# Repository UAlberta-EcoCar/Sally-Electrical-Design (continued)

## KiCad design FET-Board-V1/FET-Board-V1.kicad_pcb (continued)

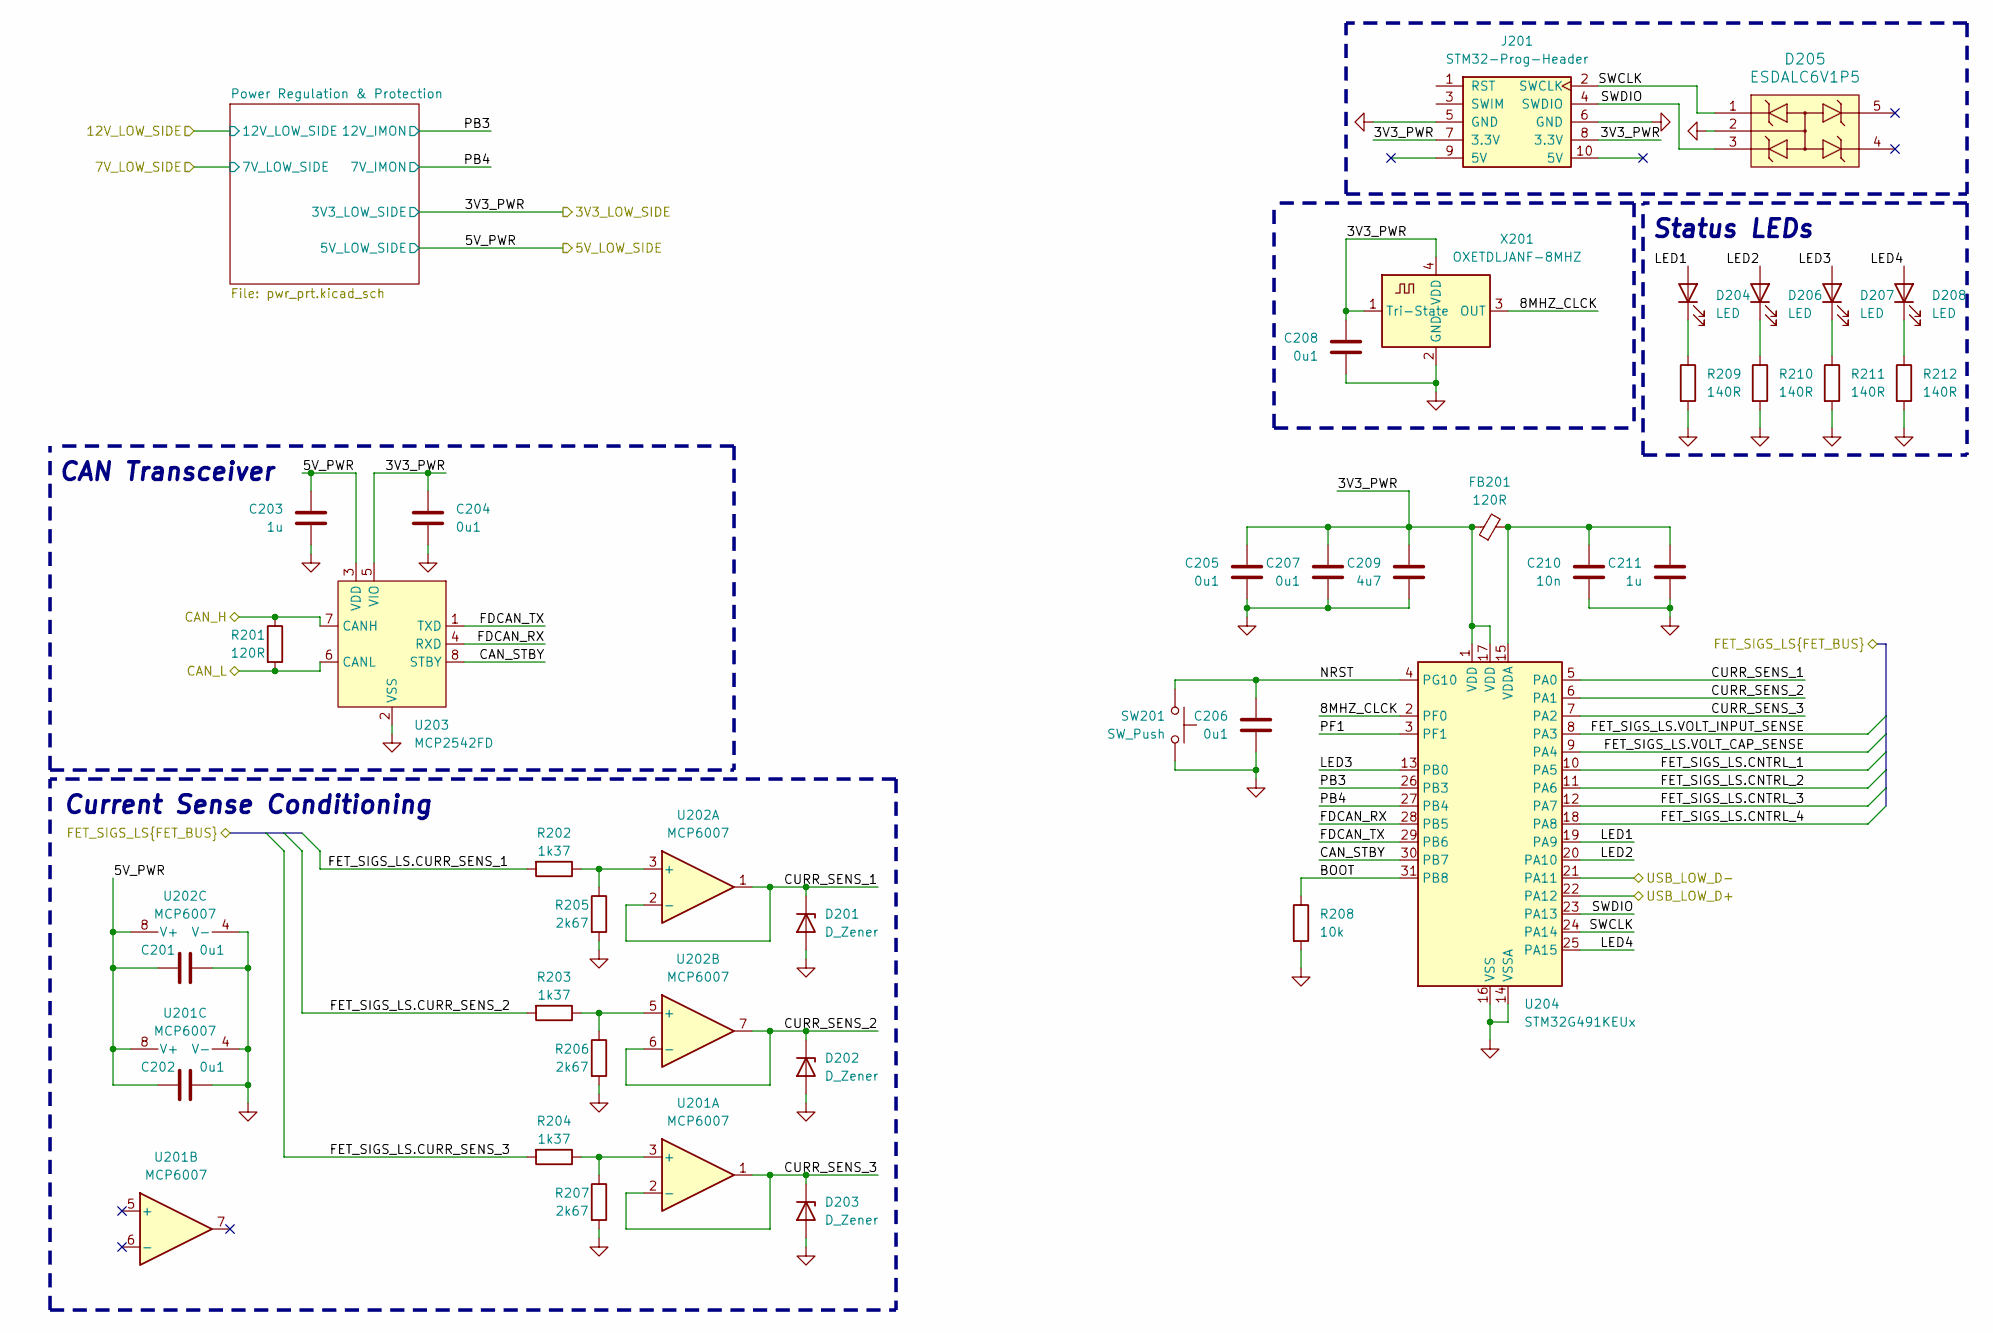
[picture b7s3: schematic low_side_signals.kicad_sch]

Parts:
C201, C202, C204, C205, C206, C207, C208: 0u1; C_0603_1608Metric
C203, C211: 1u; C_0603_1608Metric
C209: 4u7; C_0603_1608Metric
C210: 10n; C_0603_1608Metric
D201, D202, D203: D_Zener; D_0603_1608Metric
D204, D206, D207, D208: LED; LED_0603_1608Metric
D205: ESDALC6V1P5
FB201: 120R; L_0603_1608Metric
J201: STM32-Prog-Header; IDC-STM32-Prog-Header_2x05_P2.54mm_Vertical
R201: 120R; R_0603_1608Metric
R202, R203, R204: 1k37; R_0603_1608Metric
R205, R206, R207: 2k67; R_0603_1608Metric
R208: 10k; R_0603_1608Metric
R209, R210, R211, R212: 140R; R_0603_1608Metric
SW201: SW_Push; SW_PUSH_6mm
U201, U202: MCP6007; SOIC-8_3.9x4.9mm_P1.27mm
U203: MCP2542FD; SOIC-8_3.9x4.9mm_P1.27mm
U204: STM32G491KEUx; QFN-32-1EP_5x5mm_P0.5mm_EP3.45x3.45mm
X201: OXETDLJANF-8MHZ; Crystal_SMD_3225-4Pin_3.2x2.5mm

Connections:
5V_HS_NONISO: C201.1, C202.1, C203.1, U201.8 (V+), U202.8 (V+), U203.3 (VDD); also elsewhere on the board
/3V3_HIGH_SIDE: C204.1, C205.1, C207.1, C208.1, C209.1, FB201.1, J201.7 (3.3V), J201.8 (3.3V), U203.5 (VIO), U204.1 (VDD), U204.17 (VDD), X201.1 (Tri-State), X201.4 (VDD); also elsewhere on the board
/FET_SIGS_LS.CNTRL_1: U204.10 (PA5); also elsewhere on the board
/FET_SIGS_LS.CNTRL_2: U204.11 (PA6); also elsewhere on the board
/FET_SIGS_LS.CNTRL_3: U204.12 (PA7); also elsewhere on the board
/FET_SIGS_LS.CNTRL_4: U204.18 (PA8); also elsewhere on the board
/FET_SIGS_LS.CURR_SENS_1: R202.2; also elsewhere on the board
/FET_SIGS_LS.CURR_SENS_2: R203.2; also elsewhere on the board
/FET_SIGS_LS.CURR_SENS_3: R204.2; also elsewhere on the board
/FET_SIGS_LS.VOLT_CAP_SENSE: U204.9 (PA4); also elsewhere on the board
/FET_SIGS_LS.VOLT_INPUT_SENSE: U204.8 (PA3); also elsewhere on the board
/High Power Controls/CAN_H: R201.1, U203.7 (CANH); also elsewhere on the board
/High Power Controls/CAN_L: R201.2, U203.6 (CANL); also elsewhere on the board
/High Power Controls/USB_HIGH_D+: U204.22 (PA12); also elsewhere on the board
/High Power Controls/USB_HIGH_D-: U204.21 (PA11); also elsewhere on the board
/Low Power Controls/8MHZ_CLCK: U204.2 (PF0), X201.3 (OUT)
/Low Power Controls/BOOT: R208.1, U204.31 (PB8)
/Low Power Controls/CAN_STBY: U203.8 (STBY), U204.30 (PB7)
/Low Power Controls/CURR_SENS_1: D201.1 (K), U202.1, U202.2 (-), U204.5 (PA0)
/Low Power Controls/CURR_SENS_2: D202.1 (K), U202.6 (-), U202.7, U204.6 (PA1)
/Low Power Controls/CURR_SENS_3: D203.1 (K), U201.1, U201.2 (-), U204.7 (PA2)
/Low Power Controls/FDCAN_RX: U203.4 (RXD), U204.28 (PB5)
/Low Power Controls/FDCAN_TX: U203.1 (TXD), U204.29 (PB6)
/Low Power Controls/LED1: D204.2 (A), U204.19 (PA9)
/Low Power Controls/LED2: D206.2 (A), U204.20 (PA10)
/Low Power Controls/LED3: D207.2 (A), U204.13 (PB0)
/Low Power Controls/LED4: D208.2 (A), U204.25 (PA15)
/Low Power Controls/NRST: C206.1, SW201.2, U204.4 (PG10)
/Low Power Controls/PB3: U204.26 (PB3); also elsewhere on the board
/Low Power Controls/PB4: U204.27 (PB4); also elsewhere on the board
/Low Power Controls/PF1: U204.3 (PF1)
/Low Power Controls/SWCLK: D205.1, J201.2 (SWCLK), U204.24 (PA14)
/Low Power Controls/SWDIO: D205.3, J201.4 (SWDIO), U204.23 (PA13)
unnamed: D204.1 (K), R209.1
unnamed: D206.1 (K), R210.1
unnamed: D207.1 (K), R211.1
unnamed: D208.1 (K), R212.1
unnamed: R204.1, R207.1, U201.3 (+)
unnamed: R202.1, R205.1, U202.3 (+)
unnamed: R203.1, R206.1, U202.5 (+)
unnamed: C210.1, C211.1, FB201.2, U204.15 (VDDA)

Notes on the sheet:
Status LEDs
CAN Transceiver
Current Sense Conditioning

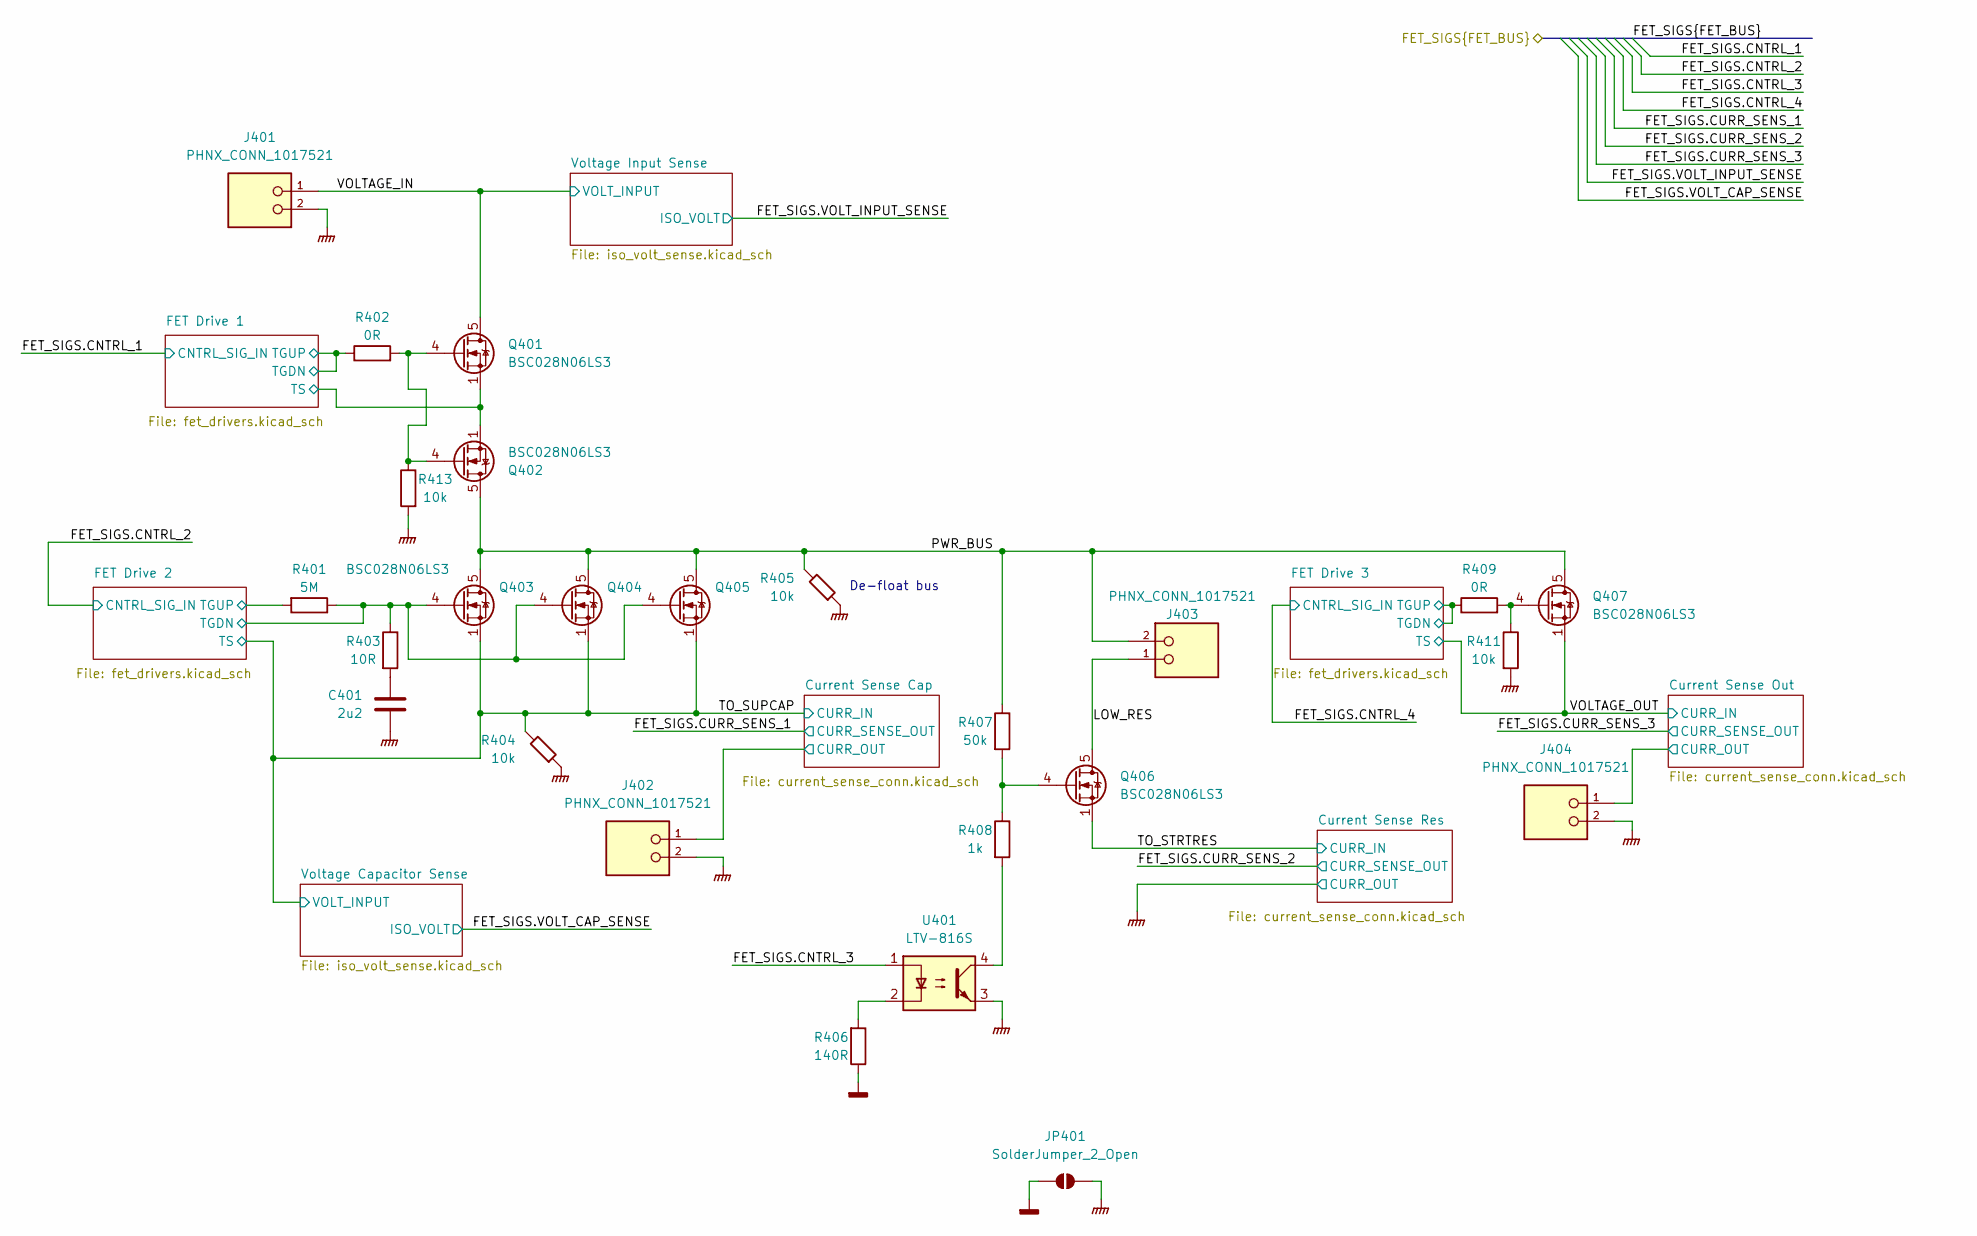
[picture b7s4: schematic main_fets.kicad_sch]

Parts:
C401: 2u2; C_0603_1608Metric
J401, J402, J403, J404: PHNX_CONN_1017521; PHOENIX_1017521; PARTREV 04.01.2018
JP401: SolderJumper_2_Open; SolderJumper-2_P1.3mm_Open_Pad1.0x1.5mm
Q401, Q402, Q403, Q404, Q405, Q406, Q407: BSC028N06LS3; TDSON-8-1
R401: 5M; R_0603_1608Metric
R402, R409: 0R; R_0603_1608Metric
R403: 10R; R_0603_1608Metric
R404, R405, R411, R413: 10k; R_0603_1608Metric
R406: 140R; R_0603_1608Metric
R407: 50k; R_0603_1608Metric
R408: 1k; R_0603_1608Metric
U401: LTV-816S; SMDIP-4_W9.53mm

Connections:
/FET_SIGS_LS.CNTRL_3: U401.1; also elsewhere on the board
/High Power Controls/Mains & FETS/Current Sense Cap/CURR_OUT: J402.1; also elsewhere on the board
/High Power Controls/Mains & FETS/Current Sense Out/CURR_OUT: J404.1; also elsewhere on the board
/High Power Controls/Mains & FETS/FET Drive 1/TGDN: R402.1; also elsewhere on the board
/High Power Controls/Mains & FETS/FET Drive 1/TS: Q401.1 (S), Q401.2 (S), Q401.3 (S), Q402.1 (S), Q402.2 (S), Q402.3 (S); also elsewhere on the board
/High Power Controls/Mains & FETS/FET Drive 2/TGDN: Q403.4 (G), Q404.4 (G), Q405.4 (G), R401.1, R403.1; also elsewhere on the board
/High Power Controls/Mains & FETS/FET Drive 2/TGUP: R401.2; also elsewhere on the board
/High Power Controls/Mains & FETS/FET Drive 3/TGDN: R409.1; also elsewhere on the board
/High Power Controls/Mains & FETS/LOW_RES: J403.1, Q406.5 (D)
/High Power Controls/Mains & FETS/PWR_BUS: J403.2, Q402.5 (D), Q403.5 (D), Q404.5 (D), Q405.5 (D), Q407.5 (D), R405.2, R407.1
/High Power Controls/Mains & FETS/TO_STRTRES: Q406.1 (S), Q406.2 (S), Q406.3 (S); also elsewhere on the board
/High Power Controls/Mains & FETS/TO_SUPCAP: Q403.1 (S), Q403.2 (S), Q403.3 (S), Q404.1 (S), Q404.2 (S), Q404.3 (S), Q405.1 (S), Q405.2 (S), Q405.3 (S), R404.2; also elsewhere on the board
/High Power Controls/Mains & FETS/VOLTAGE_IN: J401.1, Q401.5 (D); also elsewhere on the board
/High Power Controls/Mains & FETS/VOLTAGE_OUT: Q407.1 (S), Q407.2 (S), Q407.3 (S); also elsewhere on the board
GNDPWR: C401.2, J401.2, J402.2, J404.2, JP401.2 (B), R404.1, R405.1, R411.2, R413.2, U401.3; also elsewhere on the board
unnamed: C401.1, R403.2
unnamed: Q401.4 (G), Q402.4 (G), R402.2, R413.1
unnamed: Q406.4 (G), R407.2, R408.1
unnamed: Q407.4 (G), R409.2, R411.1
unnamed: R406.2, U401.2
unnamed: R408.2, U401.4

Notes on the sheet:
De-float bus

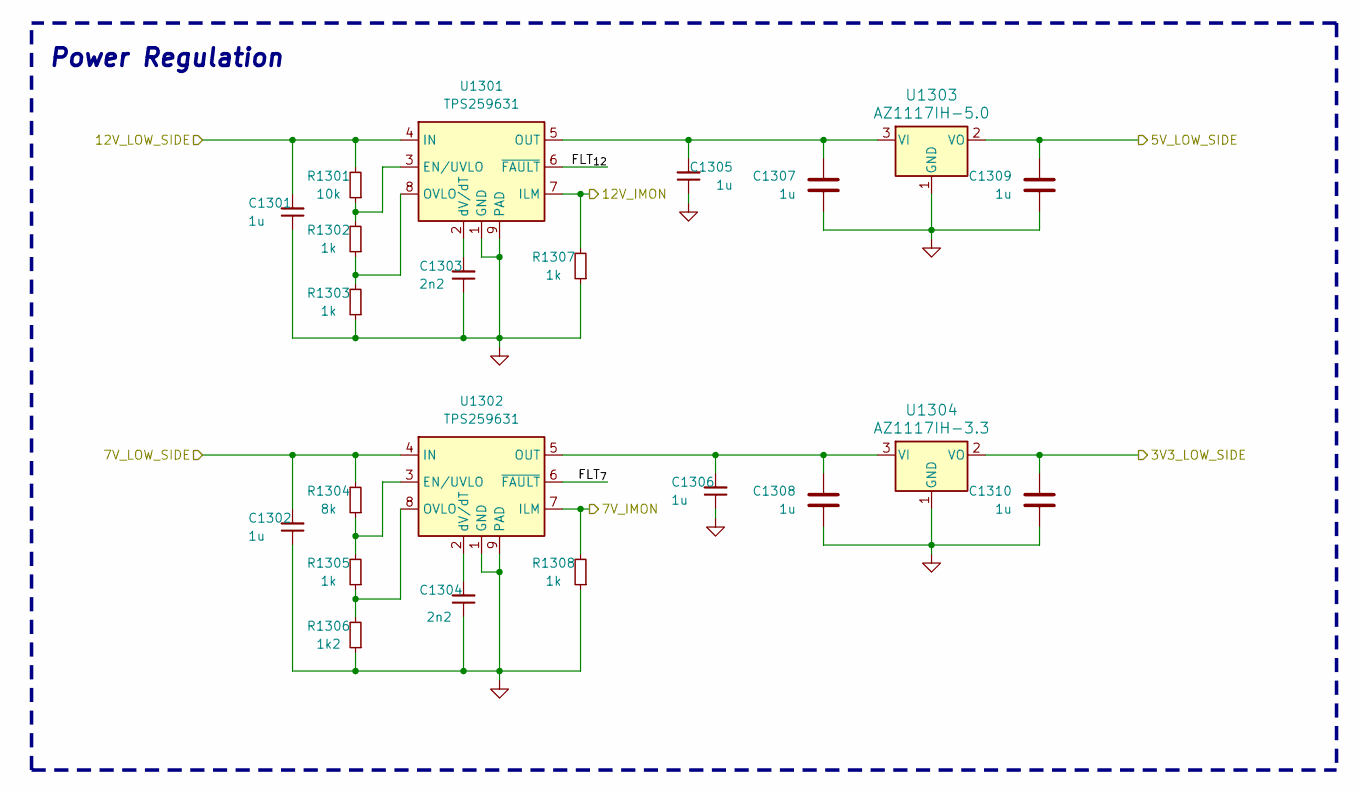
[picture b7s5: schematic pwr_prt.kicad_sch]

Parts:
C1301, C1302, C1305, C1306: 1u; C_0603_1608Metric; Part# C15849
C1303, C1304: 2n2; C_0603_1608Metric; Part# C1604
C1307, C1308, C1309, C1310: 1u; C_0603_1608Metric
R1301: 10k; R_0603_1608Metric
R1302, R1303, R1305, R1307, R1308: 1k; R_0603_1608Metric
R1304: 8k; R_0603_1608Metric
R1306: 1k2; R_0603_1608Metric
U1301, U1302: TPS259631; TI_SO-PowerPAD-8
U1303: AZ1117IH-5.0; SOT-223-3_TabPin2
U1304: AZ1117IH-3.3; SOT-223-3_TabPin2

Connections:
5V_HS_NONISO: C1309.1, U1303.2 (VO); also elsewhere on the board
/3V3_HIGH_SIDE: C1310.1, U1304.2 (VO); also elsewhere on the board
/7V_HIGH_SIDE: C1302.2, R1304.2, U1302.4 (IN); also elsewhere on the board
/12V_HIGH_SIDE: C1301.2, R1301.2, U1301.4 (IN); also elsewhere on the board
/Low Power Controls/PB3: R1307.2, U1301.7 (ILM); also elsewhere on the board
/Low Power Controls/PB4: R1308.2, U1302.7 (ILM); also elsewhere on the board
/Low Power Controls/Power Regulation & Protection/FLT_{7}: U1302.6 (~FAULT)
/Low Power Controls/Power Regulation & Protection/FLT_{12}: U1301.6 (~FAULT)
unnamed: R1301.1, R1302.2, U1301.3 (EN/UVLO)
unnamed: C1305.2, C1307.1, U1301.5 (OUT), U1303.3 (VI)
unnamed: R1302.1, R1303.2, U1301.8 (OVLO)
unnamed: C1303.2, U1301.2 (dV/dT)
unnamed: R1304.1, R1305.2, U1302.3 (EN/UVLO)
unnamed: C1306.2, C1308.1, U1302.5 (OUT), U1304.3 (VI)
unnamed: R1305.1, R1306.2, U1302.8 (OVLO)
unnamed: C1304.2, U1302.2 (dV/dT)

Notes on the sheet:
Power Regulation

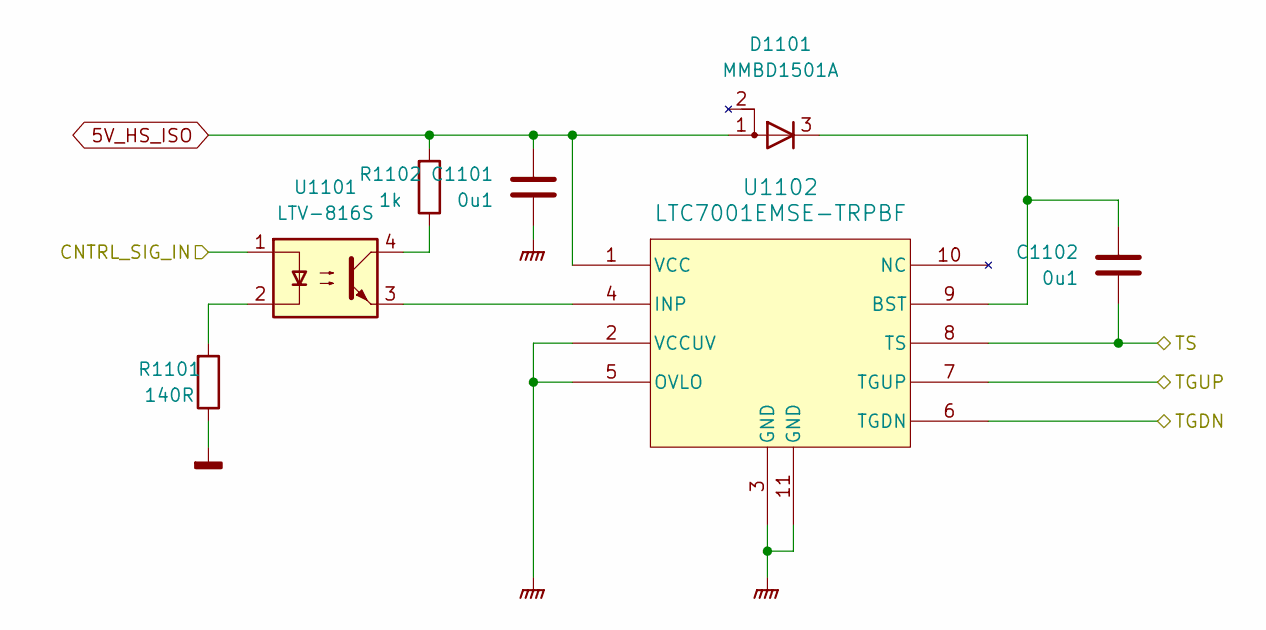
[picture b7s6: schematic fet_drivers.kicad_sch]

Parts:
C1101, C1102: 0u1; C_0603_1608Metric
D1101: MMBD1501A; SOT-23_TO-236_318-AT_OSI
R1101: 140R; R_0603_1608Metric
R1102: 1k; R_0603_1608Metric
U1101: LTV-816S; SMDIP-4_W9.53mm
U1102: LTC7001EMSE-TRPBF; 05-08-1664_ADI

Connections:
5V_HS_ISO: C1101.1, D1101.1 (A), R1102.2, U1102.1 (VCC); also elsewhere on the board
/FET_SIGS_LS.CNTRL_4: U1101.1; also elsewhere on the board
/High Power Controls/Mains & FETS/FET Drive 3/TGDN: U1102.6 (TGDN), U1102.7 (TGUP); also elsewhere on the board
/High Power Controls/Mains & FETS/VOLTAGE_OUT: C1102.2, U1102.8 (TS); also elsewhere on the board
GNDPWR: C1101.2, U1102.2 (VCCUV), U1102.3 (GND), U1102.5 (OVLO), U1102.11 (GND); also elsewhere on the board
unnamed: C1102.1, D1101.3 (K), U1102.9 (BST)
unnamed: R1101.2, U1101.2
unnamed: R1102.1, U1101.4
unnamed: U1101.3, U1102.4 (INP)

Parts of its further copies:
C901, C902, C1001, C1002: 0u1; C_0603_1608Metric
D901, D1001: MMBD1501A; SOT-23_TO-236_318-AT_OSI
R901, R1001: 140R; R_0603_1608Metric
R902, R1002: 1k; R_0603_1608Metric
U901, U1001: LTV-816S; SMDIP-4_W9.53mm
U902, U1002: LTC7001EMSE-TRPBF; 05-08-1664_ADI

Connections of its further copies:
5V_HS_ISO: C901.1, C1001.1, D901.1 (A), D1001.1 (A), R902.2, R1002.2, U902.1 (VCC), U1002.1 (VCC); also elsewhere on the board
/FET_SIGS_LS.CNTRL_1: U901.1; also elsewhere on the board
/FET_SIGS_LS.CNTRL_2: U1001.1; also elsewhere on the board
/High Power Controls/Mains & FETS/FET Drive 1/TGDN: U902.6 (TGDN), U902.7 (TGUP); also elsewhere on the board
/High Power Controls/Mains & FETS/FET Drive 1/TS: C902.2, U902.8 (TS); also elsewhere on the board
/High Power Controls/Mains & FETS/FET Drive 2/TGDN: U1002.6 (TGDN); also elsewhere on the board
/High Power Controls/Mains & FETS/FET Drive 2/TGUP: U1002.7 (TGUP); also elsewhere on the board
/High Power Controls/Mains & FETS/TO_SUPCAP: C1002.2, U1002.8 (TS); also elsewhere on the board
GNDPWR: C901.2, C1001.2, U902.2 (VCCUV), U902.3 (GND), U902.5 (OVLO), U902.11 (GND), U1002.2 (VCCUV), U1002.3 (GND), U1002.5 (OVLO), U1002.11 (GND); also elsewhere on the board
unnamed: C902.1, D901.3 (K), U902.9 (BST)
unnamed: C1002.1, D1001.3 (K), U1002.9 (BST)
unnamed: R901.2, U901.2
unnamed: R902.1, U901.4
unnamed: R1001.2, U1001.2
unnamed: R1002.1, U1001.4
unnamed: U901.3, U902.4 (INP)
unnamed: U1001.3, U1002.4 (INP)

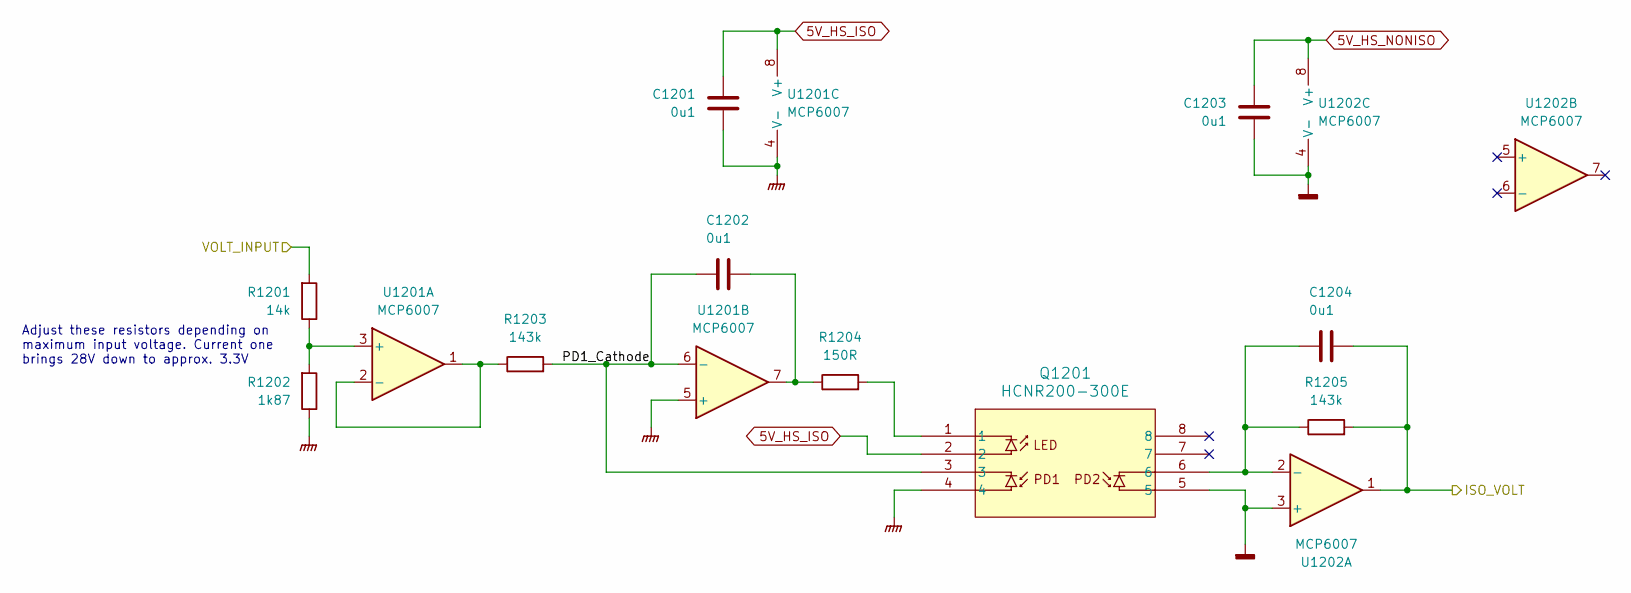
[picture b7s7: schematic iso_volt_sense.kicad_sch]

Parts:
C1201, C1202, C1203, C1204: 0u1; C_0603_1608Metric
Q1201: HCNR200-300E
R1201: 14k; R_0603_1608Metric
R1202: 1k87; R_0603_1608Metric
R1203, R1205: 143k; R_0603_1608Metric
R1204: 150R; R_0603_1608Metric
U1201, U1202: MCP6007; SOIC-8_3.9x4.9mm_P1.27mm

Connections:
5V_HS_ISO: C1201.2, Q1201.2, U1201.8 (V+); also elsewhere on the board
5V_HS_NONISO: C1203.2, U1202.8 (V+); also elsewhere on the board
/FET_SIGS_LS.VOLT_INPUT_SENSE: C1204.2, R1205.2, U1202.1; also elsewhere on the board
/High Power Controls/Mains & FETS/VOLTAGE_IN: R1201.2; also elsewhere on the board
/High Power Controls/Mains & FETS/Voltage Input Sense/PD1_Cathode: C1202.1, Q1201.3, R1203.2, U1201.6 (-)
GNDPWR: C1201.1, Q1201.4, R1202.1, U1201.4 (V-), U1201.5 (+); also elsewhere on the board
unnamed: C1202.2, R1204.1, U1201.7
unnamed: Q1201.1, R1204.2
unnamed: R1201.1, R1202.2, U1201.3 (+)
unnamed: R1203.1, U1201.1, U1201.2 (-)
unnamed: C1204.1, Q1201.6, R1205.1, U1202.2 (-)

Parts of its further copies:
C501, C502, C503, C504: 0u1; C_0603_1608Metric
Q501: HCNR200-300E
R501: 14k; R_0603_1608Metric
R502: 1k87; R_0603_1608Metric
R503, R505: 143k; R_0603_1608Metric
R504: 150R; R_0603_1608Metric
U501, U502: MCP6007; SOIC-8_3.9x4.9mm_P1.27mm

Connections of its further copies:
5V_HS_ISO: C501.2, Q501.2, U501.8 (V+); also elsewhere on the board
5V_HS_NONISO: C503.2, U502.8 (V+); also elsewhere on the board
/FET_SIGS_LS.VOLT_CAP_SENSE: C504.2, R505.2, U502.1; also elsewhere on the board
/High Power Controls/Mains & FETS/TO_SUPCAP: R501.2; also elsewhere on the board
/High Power Controls/Mains & FETS/Voltage Capacitor Sense/PD1_Cathode: C502.1, Q501.3, R503.2, U501.6 (-)
GNDPWR: C501.1, Q501.4, R502.1, U501.4 (V-), U501.5 (+); also elsewhere on the board
unnamed: C502.2, R504.1, U501.7
unnamed: Q501.1, R504.2
unnamed: R501.1, R502.2, U501.3 (+)
unnamed: R503.1, U501.1, U501.2 (-)
unnamed: C504.1, Q501.6, R505.1, U502.2 (-)

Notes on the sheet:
Adjust these resistors depending on maximum input voltage. Current one brings 28V down to approx. 3.3V

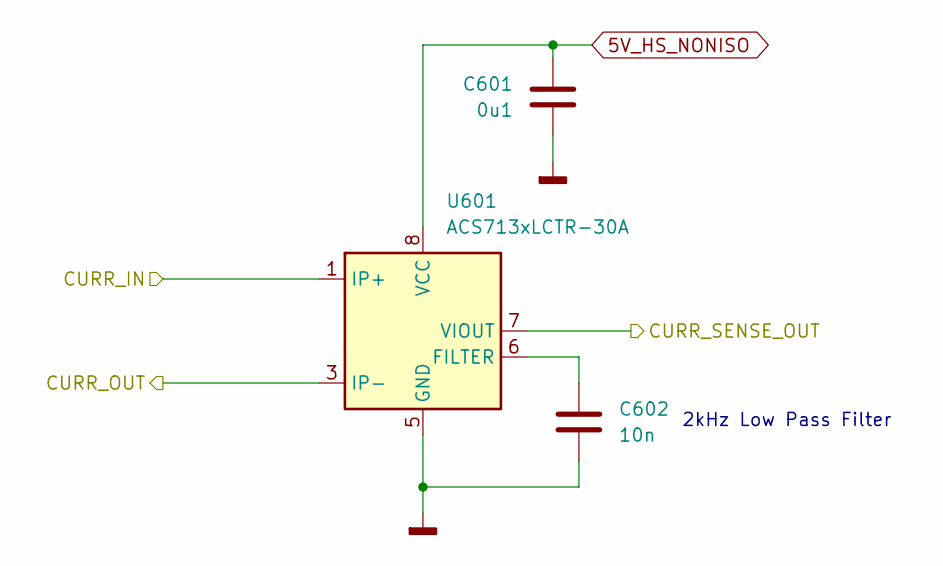
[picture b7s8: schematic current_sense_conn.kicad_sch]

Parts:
C601: 0u1; C_0603_1608Metric
C602: 10n; C_0603_1608Metric
U601: ACS713xLCTR-30A; SOIC-8_3.9x4.9mm_P1.27mm

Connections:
5V_HS_NONISO: C601.1, U601.8 (VCC); also elsewhere on the board
/FET_SIGS_LS.CURR_SENS_1: U601.7 (VIOUT); also elsewhere on the board
/High Power Controls/Mains & FETS/Current Sense Cap/CURR_OUT: U601.3 (IP-), U601.4 (IP-); also elsewhere on the board
/High Power Controls/Mains & FETS/TO_SUPCAP: U601.1 (IP+), U601.2 (IP+); also elsewhere on the board
unnamed: C602.1, U601.6 (FILTER)

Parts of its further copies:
C701, C801: 0u1; C_0603_1608Metric
C702, C802: 10n; C_0603_1608Metric
U701, U801: ACS713xLCTR-30A; SOIC-8_3.9x4.9mm_P1.27mm

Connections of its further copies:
5V_HS_NONISO: C701.1, C801.1, U701.8 (VCC), U801.8 (VCC); also elsewhere on the board
/FET_SIGS_LS.CURR_SENS_2: U801.7 (VIOUT); also elsewhere on the board
/FET_SIGS_LS.CURR_SENS_3: U701.7 (VIOUT); also elsewhere on the board
/High Power Controls/Mains & FETS/Current Sense Out/CURR_OUT: U701.3 (IP-), U701.4 (IP-); also elsewhere on the board
/High Power Controls/Mains & FETS/TO_STRTRES: U801.1 (IP+), U801.2 (IP+); also elsewhere on the board
/High Power Controls/Mains & FETS/VOLTAGE_OUT: U701.1 (IP+), U701.2 (IP+); also elsewhere on the board
GNDPWR: U801.3 (IP-), U801.4 (IP-); also elsewhere on the board
unnamed: C702.1, U701.6 (FILTER)
unnamed: C802.1, U801.6 (FILTER)

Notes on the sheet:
2kHz Low Pass Filter

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
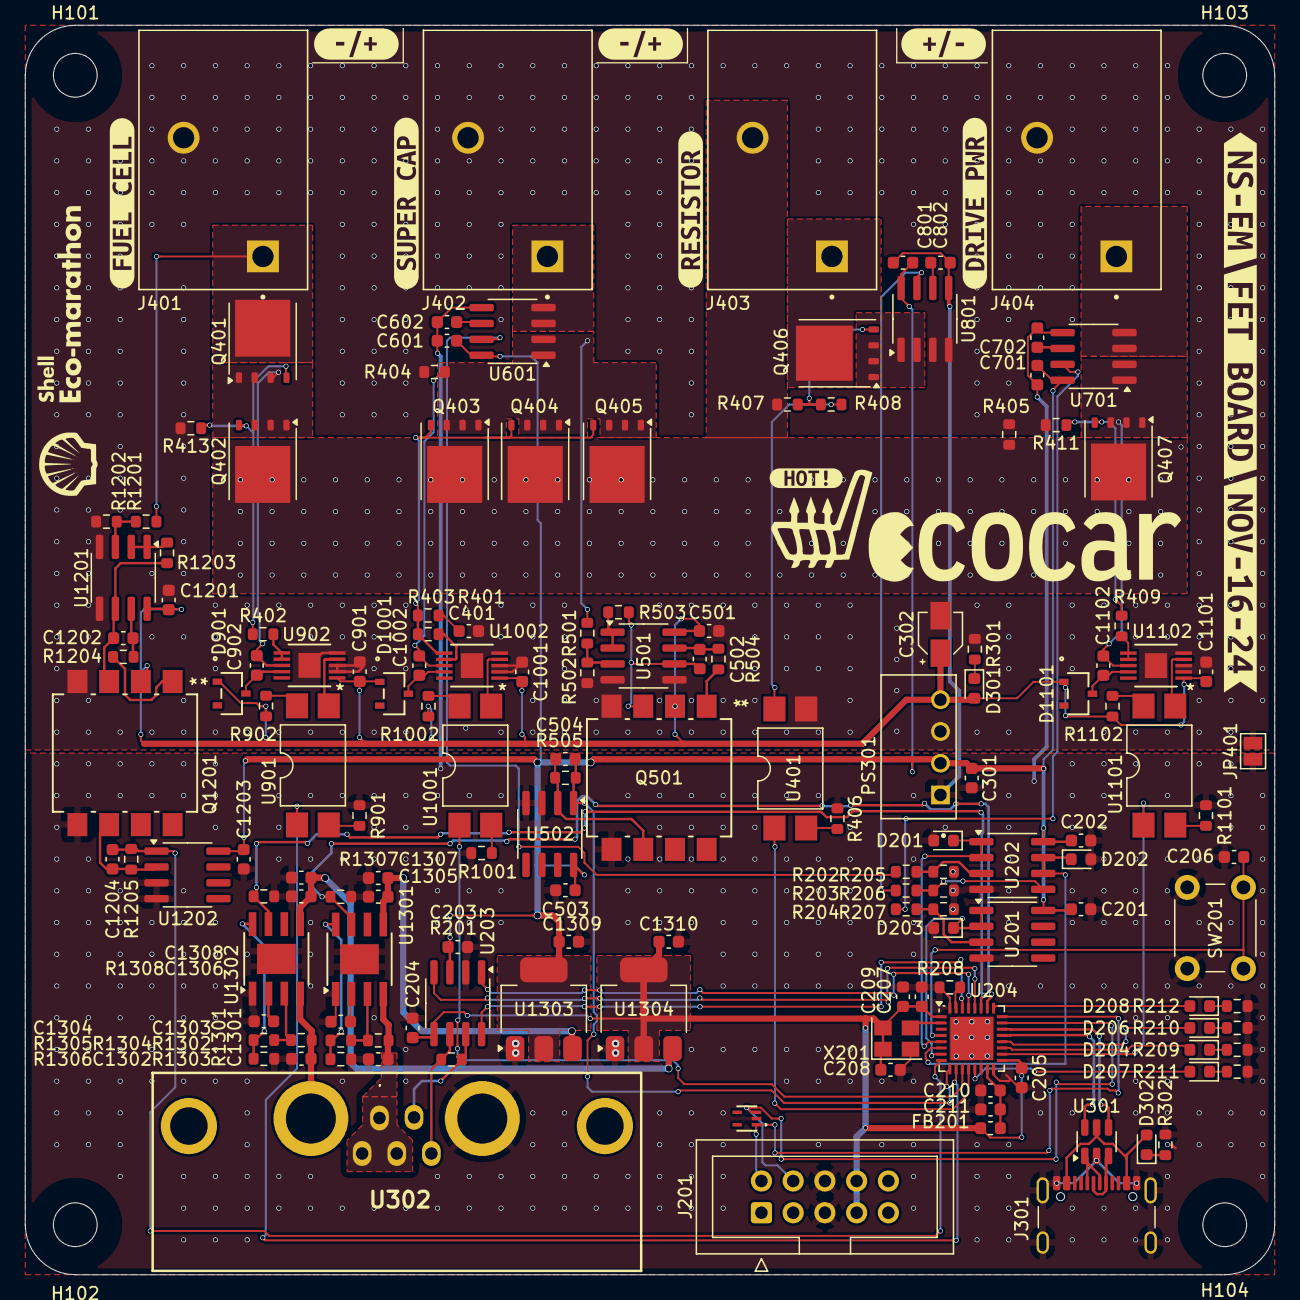
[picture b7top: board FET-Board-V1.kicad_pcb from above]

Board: 2 copper layers, 100.0 x 100.0 mm, 165 parts (0 on the bottom side), 104 nets.

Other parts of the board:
kibuzzard-673948A1: G***; kibuzzard-673948A1
kibuzzard-674285AD: G***; kibuzzard-674285AD
kibuzzard-674285BD: G***; kibuzzard-674285BD
kibuzzard-674296DE: G***; kibuzzard-674296DE
kibuzzard-6739398C: G***; kibuzzard-6739398C
kibuzzard-6742859E: G***; kibuzzard-6742859E
kibuzzard-67393673: G***; kibuzzard-67393673
kibuzzard-67428537, kibuzzard-67428537#2, kibuzzard-67428537#3: G***; kibuzzard-67428537
kibuzzard-67428592: G***; kibuzzard-67428592
